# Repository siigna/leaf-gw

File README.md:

# leaf-gw

Decision core for an inline Chassis CAN **gateway** that adds openpilot longitudinal
(gas/brake) control to a 2018–2023 Nissan Leaf (ZE1) **without disabling the
car's stock emergency braking**.

> Bench and a dedicated test car only — never a daily driver. This touches the
> brake path.

## Architecture

The comma/openpilot device, its panda, and this interceptor are **not wired
together** — everything crosses as CAN frames. Thick = the openpilot command;
dotted = the hardware fail-open bypass. Source: [`docs/architecture.mmd`](docs/architecture.mmd).

```mermaid
%% leaf-gw topology. Every link is CAN; arrows show the direction that matters.
%% Thick = the openpilot command; dotted = the hardware fail-open bypass.
flowchart TB
  subgraph COMMA["comma / openpilot"]
    direction TB
    OP["controlsd + CarController<br/>leaf_gw_long.py"]
    PANDA["panda · safety gate"]
    OP --> PANDA
  end

  subgraph INT["leaf-gw interceptor — Ocelot, 3x CAN"]
    direction TB
    CORE["gw_engine<br/>decode · arbitrate · encode · fail-open"]
    RELAY["NC fail-open relay"]
  end

  subgraph CAR["Nissan Leaf ZE1 (stock)"]
    direction TB
    ADAS["ADAS unit<br/>ProPILOT / ICC / AEB"]
    RADAR["radar + camera"]
    EPS["EPS steering"]
    VCM["VCM"]
    ABS["ABS actuator"]
    RADAR --- ADAS
  end

  VCAN{{"V-CAN<br/>(steering + openpilot 0x2B0/0x1C3)"}}
  ITS{{"ITS-CAN"}}
  ICA{{"Chassis CAN · ADAS side"}}
  ICB{{"Chassis CAN · chassis side"}}

  %% V-CAN is shared: panda already sits here. Steering goes to EPS; openpilot's
  %% real 0x2B0/0x1C3 ride the same bus and the interceptor reads them on CAN3 (a tap).
  PANDA -->|steering| VCAN --> EPS
  PANDA ==>|0x2B0 / 0x1C3 · bus 2| VCAN
  VCAN ==>|CAN3 tap| CORE
  ADAS --- VCAN
  %% ADAS private sensor bus
  ADAS --- ITS
  RADAR -.-> ITS
  %% stock request in -> arbitrated -> out to the brakes
  ADAS -->|0x2B0 / 0x1C3| ICA --> CORE
  CORE -->|0x2B0 / 0x1C3| ICB --> ABS
  ICB --> VCM
  %% hardware fail-open
  ICA -. bypass on reset .-> RELAY -.-> ICB

  classDef bus fill:#fff6d5,stroke:#b59a00
  classDef ic fill:#fde8e8,stroke:#cc6666
  classDef relay fill:#fdd6d6,stroke:#cc0000
  class VCAN,ITS bus
  class ICA,ICB ic
  class RELAY relay
```

That graph is the wiring *logically*. For **what happens over time** in one
engaged longitudinal cycle — who sends what, and the arbitration / fail-open
branches — the sequence chart (source: [`docs/sequence.mmd`](docs/sequence.mmd)):

```mermaid
%% leaf-gw: one engaged longitudinal control cycle, plus the safety branches.
%% Rendered inline by GitHub from the fenced copy in README.md.
sequenceDiagram
  autonumber
  participant OP as openpilot<br/>controlsd + CarController
  participant PA as panda<br/>safety
  participant GW as leaf-gw<br/>gw_engine
  participant AD as ADAS unit
  participant AB as ABS / VCM

  Note over OP,AB: Lateral is a separate path: OP → panda → V-CAN → EPS,<br/>it does NOT pass through the gateway. Below is longitudinal only.
  Note over AD,AB: The stock ADAS unit is never<br/>silenced — it keeps emitting its<br/>own 0x2B0 / 0x1C3 the whole time.

  GW-)PA: 0x5FF heartbeat, 50 Hz (V-CAN)<br/>no heartbeat → no long toggle, panda drops control

  loop every ~10 ms
    AD->>GW: 0x2B0 / 0x1C3 stock request<br/>(Chassis CAN ADAS side → CAN1)
    OP->>PA: desired accel (m/s²)
    alt engaged AND within bounds
      PA->>GW: real 0x2B0 / 0x1C3<br/>(V-CAN → gateway CAN3)
    else disengaged / out of bounds
      PA-xGW: blocked — panda sends nothing
    end

    alt openpilot fresh (< 50 ms) AND engaged
      Note over GW,AB: arbitration — forward whichever<br/>side commands MORE braking (op vs stock)
      GW->>AB: substituted 0x2B0 / 0x1C3<br/>(chassis side → ABS)
    else stale / disengaged
      GW->>AB: stock frame forwarded unchanged
    end
  end

  Note over AD,AB: Stock AEB = a hard 0x1C3 spike from the<br/>ADAS unit. Arbitration forwards it (stock ><br/>op), so emergency braking always wins.
  Note over GW,AB: MCU reset / power-loss → external NC relay<br/>reconnects ADAS ↔ chassis directly = stock<br/>path (no software involved).
```

And the **physical wiring** (planned; source: [`docs/wiring.mmd`](docs/wiring.mmd)).
It builds on comma's own Nissan A car harness, which plugs in between the ADAS
unit and the car loom and already brings the two halves of Chassis CAN out on
separate wire pairs; the harness box normally just joins them. The gateway sits
in that join, on a modified car-harness cable. The car's wiring is never cut,
the harness box and comma stay stock, and swapping the original cable back
undoes it. Pins and build steps are in [`HARDWARE.md`](HARDWARE.md):

```mermaid
%% leaf-gw PLANNED wiring, built on comma's Nissan A car harness (no cuts to the car).
%% The car-harness cable plugs in between the ADAS unit and the car loom and brings both
%% halves of Chassis CAN out separately; the gateway sits where the harness box would
%% join them. Pins from comma's open Nissan A drawing + the 2018 ESM. Bench only.
flowchart LR
  ADAS["ADAS unit<br/>stays LIVE (AEB intact)"]
  LOOM["car loom<br/>EPS · VCM · ABS"]

  subgraph CABLE["modified car-harness cable"]
    direction TB
    A["ADAS-side connector"]
    C["car-side connector"]
    A ---|"pass-through<br/>PT1–PT12"| C
  end

  subgraph GW["leaf-gw gateway (our add-on)"]
    direction TB
    CAN1["CAN1 · Chassis ADAS side"]
    CORE["gw_engine"]
    CAN2["CAN2 · Chassis car side"]
    CAN3["CAN3 · V-CAN tap"]
    RELAY["NC fail-open relay"]
    CAN1 --> CORE --> CAN2
    CAN3 --> CORE
  end

  subgraph STOCK["stock comma install (unchanged)"]
    direction TB
    HB["harness box<br/>V-CAN relay (steering)"]
    CF["comma four"]
    HB ---|OBD-C| CF
  end

  ADAS --- A
  C --- LOOM

  A ==>|"Chassis CAN<br/>pins 8/9 → CAN1"| CAN1
  CAN2 ==>|"Chassis CAN<br/>→ car pins 8/9"| C
  A -.->|"NC bypass"| RELAY -.-> C

  A -->|"V-CAN pins 1/2<br/>(box 16/18)"| HB
  A -.->|"tap"| CAN3
  C -->|"V-CAN (box 4/6)"| HB
  CAN2 -->|"box 8/7 → comma bus 1"| HB

  classDef stock fill:#e6f2e6,stroke:#44aa44
  classDef addon fill:#e6e6fb,stroke:#5555cc
  classDef cable fill:#fff6d5,stroke:#b59a00
  classDef relay fill:#fdd6d6,stroke:#cc0000
  class CF,HB stock
  class CAN1,CAN2,CAN3,CORE addon
  class A,C cable
  class RELAY relay
```

## How StarPilot does it, and why we don't silence

StarPilot has the one known Leaf-longitudinal implementation — but it's
**disabled** in the tree (`ALPHA_LONG_ENABLED = False`) and pinned to a single
2025 SV Plus camera firmware. It's one developer's experiment, not a shipped or
widely-run feature (StarPilot's public car list shows the Leaf for *steering*,
and says nothing about longitudinal). It still shows both that these frames
actuate on that car and why nobody kept AEB. On engage it opens a KWP2000 session
to the ADAS ECU (`0x707`) and sends *DisableNormalMessageTransmission* (`28 02`),
held open with tester-present, so the ADAS unit **goes mute**; openpilot then
transmits its own `0x2B0`/`0x1C3` on the chassis-side bus with no competing
transmitter.

That mutes **everything** the ADAS sends — including the emergency braking it
would command. No ADAS, no AEB. We reuse its accel→frame math, but treat the
numbers as a lightly-proven starting point (see the caveat below), and we do
**not** silence anything.

Instead the ADAS stays live (AEB included) and the in-line gateway **arbitrates**
per frame — dropping the ADAS's `0x2B0`/`0x1C3` only when openpilot asks for more
braking, re-stamping the stock counter so the stream stays valid. A plain
comma-harness-plus-panda can't do that (it can only add frames, not replace a
running counter-stream), which is the whole reason this is a separate in-line box
rather than a pure openpilot port.

## Why the frames are inert without the gateway

openpilot emits the real `0x2B0`/`0x1C3` on V-CAN, but on the ZE1 those ADAS
actuation signals live on **Chassis CAN** — a bus the comma harness only *listens*
to, never injects onto. So a `0x2B0`/`0x1C3` sent on a comma-accessible bus
reaches no actuator; only this interceptor, spliced into Chassis CAN, can relay them
to the ABS/VCM. Hence:

- stock car, or interceptor absent / dead → the frames go nowhere (inert);
- the gateway is the *enabling* piece, not an optimization.

Independent support: Nissan's own gateway forwarding table (published in
PCAutomotive's Black Hat Asia 2025 Leaf talk) forwards only diagnostic and a few
status IDs between buses (`0x49F`, `0x620-0x621`, `0x6FA`, `0x700-0x7FF`, …) —
`0x2B0`/`0x1C3` are not forwarded, so the car's gateway won't bridge them to the
actuators either.

That is also why mainline openpilot has no Leaf longitudinal: the only known way
to actuate was to silence the ADAS ECU and transmit on a bus that reaches the
brakes (StarPilot) — which kills AEB. This gateway actuates by splicing Chassis CAN
instead, so stock AEB stays.

**Safety gate:** across 37 cars, stock `0x2B0`/`0x1C3` show up only on panda
bus 1, never on bus 2, so nothing stock competes with openpilot's frames there.
That doesn't prove an injected frame is inert: "inert" is a property of the
*bus*, not the frame, and StarPilot proves these IDs bite on a bus that reaches
the ABS. So confirm the V-CAN segment
we transmit on is listen-only: with the interceptor absent, inject `0x2B0`/`0x1C3`
there and verify **no actuation** and that **nothing crosses to Chassis CAN**. (Same
bench step as pinning which V-CAN segment is panda bus 2.)

## What's here

`leaf_gw.c` / `leaf_gw.h` — pure, hardware-independent logic, host-testable:

- decode/encode of the two ADAS request frames, `0x2B0` (propulsion/regen → VCM)
  and `0x1C3` (friction brake → ABS actuator), plus the `0x1C3` checksum and
  `0x2B0` inverse-copy validation;
- `leaf_mode()` — fail-open state: `ACTIVE` only while engaged and an openpilot
  command arrived within the timeout; otherwise `PASSTHROUGH` (stock);
- magnitude arbitration — the gateway never silences the ADAS unit, so the stock
  request stays live; `leaf_arb_*` forward whichever side commands more braking
  and always yield to a stronger stock request. That is how stock AEB survives.
- the gateway **heartbeat** (`0x5FF`, 50 Hz, sent on the V-CAN port): openpilot
  only offers longitudinal when it sees it at startup, and panda drops control if
  it stops, so openpilot can't think it is driving when no gateway is inline.

```sh
make test
```

## Nix

```sh
nix flake check                 # C core + both Python suites + the Ocelot firmware build
nix build                       # build + host-test the core
nix build .#ocelot-firmware     # the signed panda/Ocelot image (leaf_gw.bin.signed, .elf, .bin)
echo '(0) can0 1C3#000000006400FF27' | nix run .   # phase-0 validator on a candump log
nix develop                     # host dev shell (gcc, make, python+numpy)
nix develop .#panda             # arm-none-eabi + scons, to build the Ocelot backend by hand
nix develop .#openpilot         # python 3.12 + opendbc test deps, to run the car/safety patches
nix develop .#hardware          # the board (hardware/board): KiCad, SKiDL, freerouting
nix develop .#enclosure         # the case (hardware/enclosure): .#hardware plus OrcaSlicer, gmsh
```

`nix build .#ocelot-firmware` is a sealed, offline build: it pulls the RetroPilot
ocelot tree (a pinned flake input), drops this repo's `backends/panda/` + the core
into it, registers the scons project and signs with the debug cert.

## openpilot side

`openpilot/` has the car-side piece: an opendbc `car/nissan` patch that, with longitudinal enabled, emits the car's **real** `0x2B0`/`0x1C3` frames on V-CAN (panda bus 2) — no ECU silencing, no cruise spoofing, so stock AEB stays. The inline gateway reads them off V-CAN and re-emits onto Chassis CAN with magnitude arbitration. panda bounds the frames with the standard longitudinal safety helpers. `leaf_gw_long.py` is the dependency-free mapping/packer spec (host-tested, `python3 openpilot/test_leaf_gw_long.py`); the patches wire it into opendbc. See `openpilot/README.md`.

## What's NOT here (by design)

- The firmware CAN forwarding loop (that's `backends/panda/`, built against an
  Ocelot tree — see `nix build .#ocelot-firmware`).
- The **hardware normally-closed fail-open relay** that reconnects ADAS-side
  Chassis CAN straight to the chassis side when the MCU is unpowered/reset. Software
  cannot provide power-loss fail-open; the relay is mandatory.

Those are integration + hardware and are not unit-testable on a host.

## Big caveat

The `0x2B0`/`0x1C3` layouts started from StarPilot's **disabled, firmware-pinned
2025-SV-Plus experiment**. Stock logs from 38 ZE1s have since replaced most of
it: the `0x2B0` value field, its direction and a provisional accel scale now come
from stock data. Brake pressure scaling is still StarPilot's and unverified, and
nothing has been transmitted to a car.

- **The `0x2B0` value is T = `(b2 << 4) | (b1 & 0xF)`**, a 12-bit field whose
  inverted copy sits in `b1_hi:b0`. **Higher T = more deceleration.** StarPilot's
  packer scrambled it, so its accel map was meaningless for most of its range
  (its "0 m/s²" lands at T 2304, about +0.6 m/s²). Found in two steps: the public
  US route showed the low nibbles out of order, then SHIOKAZE showed the top nibble
  was inverted too. On ~755k frames from 38 cars the inverted copy holds on every
  frame and T moves smoothly (mean step 0.18 counts; big jumps are engage/idle
  transitions).
- **Stock values:** idle / inactive T = 2595 (`dc 53 a2 .. 1b .. 03`), the
  friction-brake marker T = 3415 (`a8 27 d5 .. 5b .. 09`, only while `0x1C3`
  pressure > 0: 822 of 835 frames on the US route, 8,718 of 8,718 on SHIOKAZE's
  car), and active values in 2048..3071. "More braking" is simply the larger T,
  marker included, which is what the gateway's arbitration uses.
- **Byte 3 is a state field.** Its low nibble is always `0xC`; the top three bits
  vary (`ac`, `8c` in Park, `6c`, `4c`, …) across all cars. The gateway keeps
  stock's byte 3 when it substitutes. Bit `0x20` tracks "cruise available"
  (openpilot's `CRUISE_THROTTLE.CRUISE_AVAILABLE`): SHIOKAZE found it on their
  car, and it agrees on 99.95% of the fleet sample's 755k frames, the rest at
  on/off transitions. Byte 4 bit `0x40` is "engaged and moving".
- **`0x180` follows T about 160 ms later** (SHIOKAZE): a signed 12-bit value in
  byte 2 and byte 3's top nibble, D ≈ −0.796·T + 2067. On the fleet sample it is
  on panda **bus 0** for Nissan A cars, and the best segments fit D = −0.798·T +
  2070 at correlation −0.999 (RMSE 1.1); the median segment's RMSE is 8, and it
  departs when something else (pedal, friction brake) drives the car. Whether it's
  the VCM's actual response or just a reflection of the request is open, but
  since the comma can read it directly, the openpilot patches use it as a
  follow check: if the car slows less than openpilot asked for 1 s, openpilot
  disengages (see `openpilot/README.md`).
- **Accel scale (provisional):** fitting acceleration measured from wheel speed to
  T during ICC, across the 37-car sample, gives correlation −0.76. Zero is near
  T ≈ 2530, about +0.8 m/s² at 2272 and −0.8 at 2784, flatter in between. The
  openpilot mapping interpolates those medians. It needs an active bench or
  test-car check before anyone relies on it.
- **Public route** `44211d9f2879657d/00000024--ddf4161f21` (US `NISSAN_LEAF_IC`,
  sunnypilot, stock ICC engaged 61% of the time; 23,959 frames of each id on
  bus 1): every `0x1C3` checksum and every `0x2B0` inverse copy validates.
- **SHIOKAZE** (openpilot Discord, 2026-11-24; receive-only logs from a June 2022
  Japanese-spec ZE1 e+ G, bus 1 via the Nissan IC harness): independently
  confirmed the `0x1C3` field and checksum, worked out the `0x2B0` value field
  (T), the brake-marker state and that `b4 & 0x40` means engaged and moving, and
  found `0x707` `28 02` refused (`7F 28 11`), so StarPilot's silencing route
  doesn't work on that car.
- **Fleet check** (comma's public [commaCarSegments](https://huggingface.co/datasets/commaai/commaCarSegments)
  dataset; 3 segments from each of 31 Nissan A-harness and 6 IC-harness Leafs,
  106 segments, 635k frames of each id): zero checksum / inverse-copy failures,
  and the brake marker bytes are identical everywhere. Stock `0x2B0`/`0x1C3` appear **only on bus 1**,
  on both harnesses, never on bus 0 or 2, so stock never competes with
  openpilot's frames on bus 2. `0x5FF` never appears on any bus, so the
  heartbeat id is free.
- **What stock braking looks like.** The highest `0x1C3` pressures (680–821) are
  all ICC's standstill hold: the car stops, `0x2B0` goes to the brake marker,
  `0x1C3` ramps at ~280 counts/s, and ICC releases a few seconds later. The
  strongest braking while moving was a sudden ICC brake at 68 km/h (0 → 556 in
  under a second, about −2 m/s²) that ended when the driver pressed the
  accelerator. Arbitration handles both (stock is stronger, so stock wins); no
  AEB event is in the sample.
- Still open: the brake pressure scaling, whether `0x1C3` is total or
  friction-only braking, and what byte 3's state bits and byte 7's 2-bit field
  mean.

Check your own car with the read-only validator `tools/leaf_iccan_check.py`:
capture Chassis CAN (panda + Cabana, USB-CAN, or `candump`) and feed it the log.
It checks the `0x1C3` checksum, the `0x2B0` inverse copy, and that the `0x2B0`
value moves smoothly (a wrong bit order can pass the inverse copy but not that).

Our test car (2018 SL, 40 kWh), ECU part/version from Leaf Spy: FRONT CAMERA
`28438`/`5SA0A`, RADAR `28438`/`5SA0C`, ABS `47660`/`5SA0A`, BRAKE `47880`/`5SA1B`,
MOTOR CONTROL `292C0`/`5SA1A`. Leaf Spy's short version codes are probably a
different identifier from StarPilot's `6WK2CDB` camera pin, so the mismatch proves
nothing.

## License

MIT (see `LICENSE`), so the openpilot community can reuse it freely and because
the CAN message formats derive from MIT opendbc/StarPilot. Credits in
`ATTRIBUTION.md`.

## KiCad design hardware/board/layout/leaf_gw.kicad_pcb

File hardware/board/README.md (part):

# leaf-gw board

The inline gateway board from [SPEC.md](SPEC.md). Phase 2 is the schematic as
SKiDL code, the BOM with LCSC numbers, and the checks that stand in for a
schematic review. Phase 3 is the layout: a 75 × 50 mm, 4-layer board built by
script from the netlist, routed (pairs by script, the rest by freerouting),
checked, and turned into JLCPCB fab files. Nobody reviews the layout by eye, so
the checks are the review; each of them has a mutation test that proves it
fails on a broken board.

## Files

| path | what |
|---|---|
| `SPEC.md` | the contract |
| `ORDER.md` | how to order from JLCPCB (files, options, what to check in the preview) and how to make the board-to-box cable |
| `schematic/` | SKiDL, one module per block: `connectors`, `mcu`, `can`, `relay`, `power`, `usb`; `parts.py` holds every part with its LCSC number; `nets.py` names the nets; `board.py` builds the board and writes `out/` |
| `footprints/leaf_gw.pretty/` | project footprints for parts KiCad's library lacks (the Molex iGrid header) |
| `out/leaf_gw.net` | KiCad netlist, for phase 3 to import into the PCB |
| `out/bom_jlcpcb.csv` | JLCPCB BOM: Comment, Designator, Footprint, LCSC |
| `out/parts.csv` | the same parts with manufacturer, MPN, JLC basic/extended and stock as checked |
| `out/no_connects.csv` | every pin left unconnected on purpose, with its reason |
| `checks/` | netlist reader, safety-net checks, BOM/footprint checks, mutation tests; `layout.py` and `test_layout_mutations.py` for the PCB |
| `check.sh` | runs the schematic checks (`board-schematic`) |
| `layout/` | the PCB build: `build.py`, `placement.py`, `routes.py`, `repair.py`, `board.py` (rules, stack-up, net classes), `impedance.py`, `logo.py`, `fab.py`, `render.sh` |
| `layout/leaf_gw.kicad_pcb`, `.kicad_pro`, `.kicad_dru` | the generated board, project (net classes, JLC rules) and custom DRC rules |
| `out/fab/` | gerbers + drill, `leaf_gw-gerbers.zip`, JLC BOM and CPL, the CPL rotation corrections with their sources |
| `out/render/` | `top.png`, `bottom.png` (3D) and SVG plots of each copper layer and the assembly view |
| `check_layout.sh` | runs the PCB checks (`board-layout`) |

`out/` and `layout/leaf_gw.*` are generated, but committed so the next phase
and the board house have them; the checks fail if they are stale.

There is no `.kicad_sch`: SKiDL 2.2.1 generates schematics only for KiCad 5 to
8 (`gen_schematic` for KiCad 9 and later is an unimplemented stub), and KiCad 10's
libraries are what nixpkgs ships. The netlist is the design's source of truth
between phases.

## Running the checks

```bash
nix develop .#hardware --command ./hardware/board/check.sh            # check
nix develop .#hardware --command ./hardware/board/check.sh --update   # after editing schematic/
nix flake check                                                       # includes board-schematic and board-layout
```

`nix flake check` copies the flake's git tree, so new files have to be
`git add`ed before it sees them.

Stages, in order (one failing stage doesn't stop the others):

1. **Build + SKiDL ERC.** Any ERC error or warning fails. Unused pins are
   connected to `NC` only through `nets.nc(pin, reason)`, which records the
   reason in `out/no_connects.csv`; every other unconnected pin is an ERC warning.
2. **Freshness.** `out/` must match a fresh build byte for byte.
3. **Safety-net checks** (`checks/safety.py`), on the netlist file and
   independent of the SKiDL code (expected pin numbers come from the
   datasheets, roles from SPEC.md's tables):
   - pass-through: pins 3, 5, 13, 15, 4, 6, 10, 12 join J1.n to J2.n and nothing
     else; GND, IGN, V-CAN ADAS-side and car-side CAN1 join J1 and J2 with no
     other harness pin; IGN enters the board only through the fuse;
   - box-side J2.9 / J2.11 connect to nothing;
   - relay: pole A COM on J1.9, NC on J1.8; pole B COM on J1.11, NC on J1.7;
     NO contacts open; the two CAN1 halves are not hard-wired;
   - CAN lines: each line holds exactly its harness pins, one transceiver pin
     (CANH on H), one ESD pin, one termination jumper and, on CAN1, its relay
     contact. Termination is default-open jumper → 60.4 Ω → split midpoint
     → 60.4 Ω → jumper, midpoint → 4.7 nF → GND. Anything else on a CAN line
     fails, so a CAN line has no other path to power or ground;
   - coil driver: coil+ on the IGN-derived 5 V, coil− on the low-side FET drain
     with a flyback diode; the gate net holds only the AND output and one
     pull-down; AND input A is PB12 with one pull-down; input B is the
     open-drain watchdog RESET, which is also MCU NRST; WDI is driven only by the
     kick pin;
   - USB isolation: the coil supply is not DC-reachable from VBUS (diodes
     forward only), and it is reachable from IGN;
   - MCU pins, by LQFP64 pin number: CAN1/2/3 RX/TX and standby go to the
     transceiver on the right bus, PA1 to the IGN divider, PA11/PA12 to USB D−/D+;
     no two table pins share a net.
4. **BOM + footprints** (`checks/bom.py`): every assembled part has an LCSC
   number and a JLC library type; designators are unique in the netlist and in
   the CSV; the CSV lists exactly the assembled parts; parts off the BOM are bare
   copper (test pads, solder jumpers) with a reason. Every footprint exists and
   has a pad for each connected pin.
5. **Mutation tests** (`checks/test_mutations.py`): 41 in-memory mutations of
   the real netlist, each of which must make its check fail (relay NC/NO
   swapped, poles crossed, box 9/11 connected, gate pull-down dropped, gate fed
   from PB12 directly, watchdog off NRST, CAN1 on the CAN2 pins, RX/TX swapped,
   resistor from a CAN line to GND, closed termination jumper, coil on the USB
   rail, OR diode reversed, missing LCSC, duplicated designator, pin without a
   pad, and more), plus the unmutated netlist passing everything.

## Layout (phase 3)

### Pipeline

`layout/build.py` builds `layout/leaf_gw.kicad_pcb` from `out/leaf_gw.net`.
It takes about 40 minutes, most of it in the pre-route searches and freerouting.

1. **Project and rules.** It writes `leaf_gw.kicad_pro` (net classes, the JLC
   minimums, DRC severities) and `leaf_gw.kicad_dru` (12 V track width, via
   drill and ring).
2. **Board.** A 75 × 50 mm outline with 1 mm corner radii goes on a 4-layer
   board. Every footprint comes from the netlist with its fields and pad nets,
   placed by `placement.py`, all on the top side. Two M2 mounting holes go in
   opposite corners.
3. **Critical routes by script** (`routes.py`). The four CAN pairs and the USB
   pair are drawn coupled at the impedance geometry, split evenly around their
   tap clusters, and length-matched with small rectangular bumps (`TUNE`).
   freerouting has no differential-pair support, so the pairs never reach it.
   The same file draws a few hand routes into spots freerouting can't reach:
   CC1, SWDIO, the MCU supply pins boxed in by their neighbours, and the
   USBLC6's VBUS via. It also draws the short local copper that must not be
   left to chance (`LOCAL_LINKS`, `POWER_LINKS`): each transceiver's VCC and
   VIO cap, U5/U6's supply cap, the termination chains off the relays' NO
   contacts, the two coils in parallel, and the buck's own copper (switch
   node, hot-loop VIN and GND, bootstrap, feedback and its sense at the output
   cap, the input protection).
4. **Fanout** (`build.fanout`). Each SMD pad on GND or +3V3 gets a via to its
   plane. So does each signal pin the CAN lines close in on (`routes.FANOUT_SIGNALS`).
   A spot is accepted only where the via's In1 antipad stays clear of the GND
   plane under the pairs, and where its ring keeps `board.VIA_PAD_WEB` from
   every SMD pad, its own net's included (no via in or touching a pad).
5. **Pre-routes** (`repair.preroute`, list in `routes.PREROUTE`). The
   transceivers' STB lines and the MCU's top-row CAN pins and BOOT0 are
   routed first with the
   grid router (step 8), while the board is still open. Each search is capped
   (8 M expansions, 900 s, a box 14 mm around its ends) and logs why it gave
   up; whatever fails is left to freerouting.
6. **Silkscreen.** Library silkscreen that would print on a pad or overlap
   other silkscreen is dropped (`silk_cleanup`). Then the logo, the text, the
   back-side pin names and the bench warning go on, and a cathode bar beyond
   pad 1 of every diode and LED whose library mark was dropped
   (`polarity_marks`).
7. **freerouting.** The board is exported to DSN and the DSN is patched. In1
   and In2 become power layers, so nothing routes on them. The pairs and the
   plane nets leave the network, and their copper turns into keepouts. Each
   pair also gets a via keepout as wide as the reference-plane check needs,
   and the strip between J2's edge-side pin row and the board edge gets one
   too (`routes.VIA_KEEPOUT`: via antipads there pinch the In2 plane). New vias
   use a padstack 0.05 mm wider than the real one, so freerouting's via-to-via
   clearance also keeps 0.5 mm hole to hole; they are shrunk back after the
   import. The DSN also says `via_at_smd off`, and B.Cu under the buck's
   switch node and L1 is a keepout (`build.quiet_zone`). freerouting 2.5 then runs single-threaded (`-mt 1`) with a fixed
   pass count (wall time capped at 900 s), and the SES is imported back.
8. **Repair.** If freerouting leaves anything open, `repair.py` routes it on a
   0.05 mm grid (A* over F.Cu and B.Cu with vias, capped at 4 M expansions
   and 240 s per search), clear of every other net's copper, of the via
   keepouts and, for its vias, of every SMD pad. On the committed board freerouting finished everything, so the
   repair had nothing to do.
9. **Clean-up and zones.** Tracks that freerouting necked below the minimum
   are widened back where there is room (`widen_necks`); one that can't be
   widened is taken out and its gap repaired at full width. Every lone via
   on a 12 V or 5 V net gets a twin 0.85–1.4 mm away, joined on both layers
   (`twin_power_vias`). The zones go on: In1 solid GND, In2 solid +3V3, and
   GND pours on F.Cu and B.Cu with thermal reliefs, and are filled. Then
   `stitch_gnd` puts GND vias along the board edge about every 5 mm where
   both pours leave room, gives every outer pour island at least two vias to
   In1, and cuts an island that can't take them out of its pour (a rule
   area), unless a pad hangs on it alone. Then `drop_dangling` deletes every via joined on
   fewer than two layers and every track with a loose end (freerouting's
   leftovers, fanout and escape vias it bypassed), one at a time and only if
   nothing comes apart without it.
10. **Normalise.** Every UUID is renumbered in file order from a fixed
   namespace, so the same inputs give the same file, and `leaf_gw.kicad_pro`
   is written again after pcbnew's save (which rewrites it).

`layout/fab.py` then writes `out/fab/` and `layout/render.sh` writes
`out/render/`.

### Placement

`placement.py` and `routes.py` are drawn on the first, 59 × 39.5 mm board.
That was too dense: freerouting and the repair left 1 to 3 connections open
on every run. `board.spread()` opens the drawing up into the 75 × 50 mm
outline by moving whole blocks rigidly. It adds 1, 10 and 5 mm in x at three
vertical cuts (J1's pin field | the clusters and MCU, ADAS side and relay |
car side, car side | J2's pin field), 3 mm in y below the top band and 7.5 mm
below CAN0, between the headers. Groups that sit in room the spread opened,
or would straddle a cut, are placed and routed in board mm after the spread
(`placement.CAR`, `ADAS_TERM`, `POWER`; `routes.car_side`, `POWER_LINKS`):
the car side right of K1 with K2, both termination chains, the power entry
and the buck, the LDO strip, and U5/U6's supply caps. Nothing in them moves
with a cut. Only straight runs along the shift cross a
cut, so every scripted route keeps its shape (`routes._spread` asserts it),
and the pair lengths change equally on both lines. A 70 × 45 mm version of
the same spread still left one connection open (CAN2_STB, then RELAY_GATE),
so the board went to the 75 × 50 mm limit.

The two headers sit on the short edges in the same orientation: rotation 90,
pin 1 at the bottom, the even row toward +x. Pin n of J1 and pin n of J2 are
then at the same height, so the pass-through nets run straight across. The
blocks are:

| where | what |
|---|---|
| top left | CAN2 (V-CAN tap): ESD array, transceiver 3, termination, between the CAN2 lines; under it the LDO with its caps |
| top right | the buck as one group (below); right of it the power entry: reverse diode, TVS, PTC tapping the B.Cu IGN lane; the power LED; test pads TP7–TP10 |
| middle left | CAN1 ADAS side next to J1: ESD array, transceiver 1 |
| middle | K1 on all four CAN1 lines, between the two halves; the ADAS-side termination along its top, off its NO contacts |
| middle right | K2 on the car-side lines, the car-side termination beside its NO contacts, then the car-side ESD array and transceiver 2 |
| across | CAN0, straight through |
| bottom | MCU (crystal and decoupling at its pins), USB-C on the bottom edge with the USBLC6 beside it, relay driver and watchdog, SWD pads, DFU button, ignition sense |

Each CAN tap cluster sits between its own two bus lines, L over the top and H
underneath. The ESD array (rotation 180, pads 1/2 on its right) faces the
transceiver's CANL/CANH pins (rotation 180, pins 6/7 on its left) across a
0.77 mm channel. Short spurs drop into that channel from each line. This is
how the lines tap the cluster without crossing each other, so the CAN copper
needs no vias at all.

The buck (U7) is one tight group: D8 right above the SW pin, the input caps
right of VIN with C26 first and their GND pads under D8's anode (hot loop
C26–VIN–SW–D8–GND 10.3 mm², from 60.9), L1 beside D8 on the same SW copper
as the bootstrap cap, the output caps under L1's output, and the feedback
divider between them and the FB pin, so FB, CB and the sense at C28 are a few
mm on F.Cu. The output caps' GND is on the far side of the group from D8's
anode (about 12 mm, through the pour and In1 0.2 mm below); keeping both
loops on the same side would have pushed the sense trace and the input feed
across each other.

K2 (rotation 90) takes the car pair through the channel between its pad
rows: the L line leaves up through COM_B and the H line down through COM_A,
so the contacts sit on the lines with no stub, and its NO pads face the
car-side jumpers. Its coil pads sit next to K1's; the two coils are joined on
F.Cu (+5V_IGN) and share the driver and flyback diode.

The relay is DPDT, pole B (L) in the left column and pole A (H) in the right.
ADAS L lands on COM_B from the left. ADAS H passes between COM_B and NC_B to
COM_A from inside. Car L lands on NC_B and leaves between COM_A and NC_A. Car
H passes under NC_B to NC_A. None of the four lines crosses another.

### Stack-up and impedance

JLC04161H-7628, 1.6 mm, as listed at
[jlcpcb.com/impedance](https://jlcpcb.com/impedance) (read 2026-11-26):

| layer | role | copper | to next layer |
|---|---|---|---|
| L1 F.Cu | signal (pairs) | 35 µm | 7628 prepreg 0.2104 mm, εr 4.4 |
| L2 In1.Cu | GND plane | 15.2 µm | core 1.065 mm, εr 4.6 |
| L3 In2.Cu | +3V3 plane | 15.2 µm | 7628 prepreg 0.2104 mm, εr 4.4 |
| L4 B.Cu | signal | 35 µm | |

`layout/impedance.py` computes the pairs as edge-coupled microstrip on L1 over
L2. The single line uses Hammerstad & Jensen with the finite-thickness
correction; the coupling uses Garg & Bahl's even/odd capacitances. Both are
static and ignore solder mask, which lowers the impedance by a few percent.
IPC-2141A is shown as a coarse cross-check:

| pair | width | gap | Zdiff (Garg-Bahl) | IPC-2141A | target |
|---|---|---|---|---|---|
| CAN (4 pairs) | 0.19 mm | 0.20 mm | 120.0 Ω | 111 Ω | 120 Ω |
| USB D+/D− | 0.35 mm | 0.20 mm | 89.8 Ω | 81 Ω | 90 Ω |

As a sanity check, the same single-line model puts 50 Ω at 0.36 mm on this
stack-up. Before ordering, confirm both pairs in JLC's own impedance
calculator, which includes the mask. You may also order "impedance control"
on this stack-up (see Ordering).

### JLCPCB rules

The rules come from [jlcpcb.com/capabilities/pcb-capabilities](https://jlcpcb.com/capabilities/pcb-capabilities)
(multilayer, 1 oz, read 2026-11-26). They live in `layout/board.py` and are
written into the project file:

| rule | board | JLC |
|---|---|---|
| track / space | 0.127 / 0.127 mm (SPEC); net classes 0.15 clearance | 0.09 / 0.09 mm |
| via | 0.3 mm drill / 0.6 mm pad (0.15 mm ring) | 0.15 / 0.25 mm min; ring ≥ 0.15 mm absolute minimum |
| hole to hole | 0.5 mm | 0.2 (vias), 0.45 (pads) |
| copper to routed edge | 0.25 mm | 0.2 mm |
| silkscreen | 0.15 mm line, 1.0 mm text, 0.15 mm from pads | the same |
| 12 V input (IGN, IGN_FUSED, VIN_PROT, VIN12_10/12) | ≥ 0.5 mm (custom DRC rule) | |

Net classes: CAN 0.19 mm, USB 0.35 mm, 12V 0.67 mm, Power 0.4 mm and Default
0.17 mm. Two of these are wider than the floor on purpose. Where freerouting
squeezes between pads it necks a track to about 3/4 of its class width, and
these class widths keep a necked track at or above 0.127 mm and 0.5 mm.

### Checks

`check_layout.sh` (flake check `board-layout`) runs these stages:

1. **Self-checks.** The impedance geometries are within 3 % of target, and
   the logo conversion works: the cleaned leaf has no line or gap under
   0.15 mm, a keyholed polygon with holes survives the round trip, and the
   SVG path parser gets an arc's area right and still reads the old snail.
2. **Freshness.** `leaf_gw.kicad_pro` and `.kicad_dru` match the generator.
3. **DRC.** `kicad-cli pcb drc --severity-all` reports 0 errors, 0 warnings
   and 0 unconnected items, against the JLC rules above. Schematic parity is
   left to stage 4, because there is no schematic.
4. **Layout checks** (`checks/layout.py`). They work on pcbnew's own copper
   shapes, independent of the build scripts:
   - parity: every netlist part is on the board with its footprint, every pad
     has the netlist net of (ref, pad), and pads the netlist leaves open have
     none. Nothing extra is allowed except H1, H2 and LOGO;
   - every footprint is on the top side;
   - pairs: all pair copper is on F.Cu, with no via, at the impedance width.
     The only narrower pieces allowed are the USB plug-flip links within
     2.5 mm of J3. Outside the listed `routes.UNCOUPLED` zones (header pin
     fields, the cluster splits, the relay, the USBLC6, the tuning bumps),
     each line sits exactly width + gap from its partner (±10 µm);
   - mismatch: the H/L copper length from the reference end to each bus end
     and transceiver is under 1 mm. The lengths are computed over the track
     graph and printed;
   - reference plane: under every pair track, the In1 GND fill covers the
     track width plus one prepreg height (0.21 mm) on each side, so there is
     no split, no void and no other net's antipad. The header pin fields and
     the USBLC6 are exempt; their own PTH and via antipads are unavoidable;
   - 12 V: every IGN, IGN_FUSED, VIN_PROT and VIN12 track is ≥ 0.5 mm;
   - keepouts: no other courtyard sits within 0.5 mm of either header body
     (the mating face). The USB-C front is at the bottom edge (−0.1 to
     +0.6 mm), and no courtyard sits in the 12.35 mm plug-overmold zone along
     that edge;
   - copper safety: islands are built by physical overlap of every pad,
     track, via and zone fill, per layer and through the holes, ignoring
     their net labels. No island may join two netlist nets, or a net and an
     open pad, and every net must be one island. The relay COM pads reach
     only the ADAS-side lines and the NC pads only the car side, so the two
     CAN1 halves touch only through the contacts. Box pins J2.9 and J2.11
     touch no track or zone on any layer;
   - silkscreen: the logo, as drawn on the board, has lines and gaps of at
     least 0.15 mm, is about 12 mm wide and sits on the top. No silkscreen on
     either side comes within 0.15 mm of a solder-mask opening or runs off
     the board;
   - pin labels: each header has exactly one back-side label per pin row
     ("n … / n+1 …"), its centre within 0.3 mm of that row's pins, on the
     header's inner side with its near end 0.15 to 5 mm from the pads;
   - In2: only short hops on the +3V3 plane, which stays one region with no
     neck under 1.0 mm (see "Known limits");
   - vias and pads: no via ring overlaps or touches any SMD pad, its own net's
     included, so the hole edge keeps at least 0.15 mm of copper web;
   - polarity marks: every diode and LED has top silkscreen within 1 mm beyond
     pad 1 (the cathode), across at least half the pad's width;
   - power vias: every via on a 12 V or 5 V net has a second via of its net
     within 1.5 mm (the USBLC6's VBUS reference pin, boxed in by the USB pair
     and carrying no load current, is exempt), and the switch node has none;
   - GND stitching: every F.Cu or B.Cu GND pour island reaches In1 through at
     least two vias or plated GND pins, and along the board edge (1 mm in),
     wherever both pours leave room for a via, one sits within 3.5 mm
     (except the via keepout strip beside J2);
   - 12 V off the MCU: no VIN_PROT or IGN_FUSED copper within 3 mm of U1's
     courtyard;
   - switch node: nothing but GND on B.Cu under the buck's switch node and
     L1 (0.3 mm around), and no other net on F.Cu inside L1's courtyard.
5. **Mutation tests** (`checks/test_layout_mutations.py`). Each test loads the
   real board, breaks it in memory and asserts that its check fails for the
   intended reason:

   | mutation | caught by |
   |---|---|
   | two pads' nets swapped | parity |
   | a footprint deleted | parity |
   | an extra footprint added | parity |
   | a capacitor flipped to the bottom | top side |
   | a CAN0_L run moved 0.3 mm | pairs (uncoupled) |
   | a via dropped into CAN0_H | pairs (via) |
   | a CAN2_L run moved to B.Cu | pairs (layer) |
   | a USB D+ run narrowed to 0.2 mm | pairs (width) |
   | a 1.2 mm detour added to CAN0_H | mismatch |
   | a 1 mm slot cut in In1 under CAN0 | reference plane |
   | the In1 GND zone deleted | reference plane |
   | an IGN track narrowed to 0.3 mm | 12 V width |
   | a resistor moved onto J1's mating face | keepouts |
   | J3 moved 2 mm in from the edge | keepouts |
   | a resistor moved into the USB plug zone | keepouts |
   | a track across relay COM_A to NC_A | copper safety (short) |
   | the ADAS L track to COM_B removed | copper safety (open) |
   | a track touching J2.9 | copper safety (box pin) |
   | a pass-through loop's tracks removed | copper safety (open) |
   | the logo moved onto MCU pins | silkscreen (pad opening) |
   | a 0.1 mm line added to the logo | silkscreen (line width) |
   | a J2 pin label moved 1 mm off its row | pin labels |
   | a relay K2 COM track removed | copper safety (K2) |
   | a GND fanout via moved onto C26's pad / its ring 0.2 mm into the pad | vias and pads |
   | D6's cathode mark removed | polarity marks |
   | a +5V_IGN via's twin removed | power vias |
   | a via on the switch node | power vias |
   | one of the two vias of a GND pour island removed | GND stitching (island) |
   | the GND vias along the middle of the top edge removed | GND stitching (edge) |
   | a VIN_PROT track across the MCU | 12 V off the MCU |
   | an IGN_SENSE track on B.Cu under L1 | switch node |
   | a 10 mm SWDIO track on In2, In2 split, In2 neck | In2 |
   | a CAN0_H stub run into CAN0_L, saved and run through `kicad-cli pcb drc` | DRC |

   The unmutated board must pass every check.
6. **Fab outputs.** `fab.py` must reproduce `out/fab/` byte for byte. The fab
   BOM must match `out/bom_jlcpcb.csv` part for part (LCSC, footprint, MPN),
   every BOM line must have an LCSC number, and the CPL must list exactly the
   BOM parts.

`./check_layout.sh --rebuild` also builds a fresh board in /tmp/lgw/rebuilt
and requires it to pass the DRC and the layout checks. That takes about 40
minutes, so the flake check leaves it out. Fresh builds don't reliably
converge yet (see "Known limits").

Silkscreen-only changes don't need a re-route: `kicad-python build.py
--silk-only` (in `layout/`) redraws the logo and all silkscreen text on the
saved board from `placement.py` and `logo.py` and leaves copper and fills
alone.

### Regenerating

```bash
nix develop .#hardware --command ./hardware/board/check_layout.sh --update   # rebuild board, fab, renders; then check
nix develop .#hardware --command ./hardware/board/check_layout.sh            # check only
```

After editing `placement.py` or `routes.py`, look at the mismatch report that
`checks/layout.py` prints and adjust `routes.TUNE` if a pair moved.

### Ordering (JLCPCB)

**PCB:** upload `out/fab/leaf_gw-gerbers.zip`. Pick these options:

- Layers 4, dimensions 75 × 50 mm (detected), thickness 1.6 mm, FR-4.
- Impedance control yes, stack-up JLC04161H-7628. That is the stack-up the
  pair widths were computed for.
- Via covering tented, which is what the board assumes; silkscreen runs over
  vias.
- Green mask, white silkscreen. Surface finish: HASL lead-free, or ENIG for
  the 0.5 mm-pitch MCU.
- Remove order number: "specify a location" or pay to remove it. There is no
  marked spot, so pick "remove".
- Board outline tolerance standard. Leave edge rails and tooling holes to
  JLC's assembly options.

**Assembly:** PCBA on the top side, Standard (not Economic). The board has
through-hole headers and extended parts. Upload:

- `out/fab/leaf_gw-bom.csv` as the BOM. All 37 lines have LCSC numbers.
- `out/fab/leaf_gw-cpl.csv` as the CPL. Mid X/Y are in mm from the board's
  bottom-left corner, all parts on the top.

In the placement preview, check every part listed as "verify" in
`out/fab/leaf_gw-cpl-corrections.csv`. Those are the relay, the MCU, the
SOT-23-6 parts, the iGrid headers and every polarized two-terminal part,
whose rotations come from footprint-family tables rather than part-specific
evidence. Adjust the rotations there if a body or pin-1 mark is off. The
headers J1/J2 are through-hole on the top side; JLC solders those by
selective/wave or by hand as part of Standard PCBA. Buy the MCU (C468260,
90 in stock on 2026-11-26) early.

**The box cable** is a separate order. It is a 501646-1800 receptacle on both
ends, crimped 501647-1000 terminals, pin n to pin n, positions 9 and 11 left
empty, 26 AWG, about 100 mm. Order it from a harness service with a drawing,
for example LCSC Cable ([lcsccable.com](https://lcsccable.com), no MOQ). See
"Connectors" above for the part numbers. Leaving positions 9 and 11 empty is
part of the safety design, so state it on the drawing.

### Known limits of the layout

- **Routing is complete.** The committed board is a fresh `build.py` output
  (no hand edits): DRC 0 errors, 0 warnings, 0 unconnected, and every layout
  check and mutation test passes. The pre-order review revision was validated by two fresh
  `check_layout.sh --rebuild` runs on 2026-11-27, both valid on the first
  routing attempt; an earlier pair had one run leave SWCLK unrouted on all six
  attempts, so SWCLK is now pre-routed (`routes.PREROUTE`).
- **The buck's output loop closes through the pour.** The output caps' GND
  sits about 12 mm from D8's anode, on the far side of the group (see
  "Placement"); the return runs in the F.Cu pour and the In1 plane 0.2 mm
  below. The input hot loop, the one with the fast edges, is 10.3 mm².
- **USBLC6 VBUS has one via.** U9's VBUS pin is the clamp's reference and
  carries no load current; it is boxed in by the USB pair, so its single via
  is exempt from the twin-via rule. The load path from J3 to D10 has twins.

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
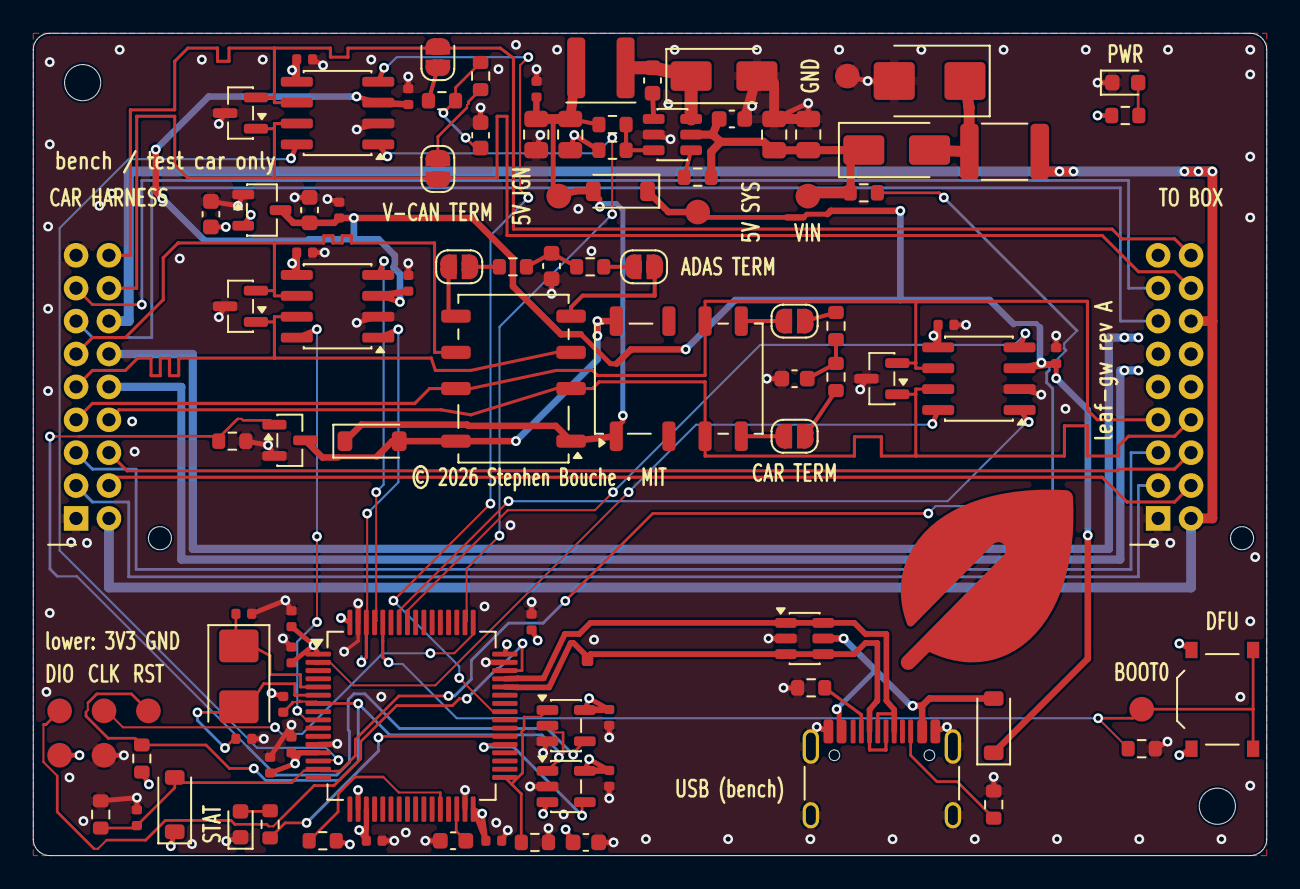
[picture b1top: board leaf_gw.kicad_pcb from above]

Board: 4 copper layers, 75.0 x 50.0 mm, 104 parts (0 on the bottom side), 68 nets.

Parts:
C1, C8, C31, C33: 4.7uF 16V; C_0603_1608Metric
C2, C3, C4, C5, C6, C7, C13, C14, C16, C17, C19, C20, C22, C23, C30, C34: 100nF 16V; C_0402_1005Metric
C9, C32: 1uF 25V; C_0402_1005Metric
C10, C11: 30pF C0G; C_0402_1005Metric
C12: 10nF 50V; C_0402_1005Metric
C15, C18, C21: 4.7nF 50V; C_0603_1608Metric
C24, C25: 2.2uF 50V X7R; C_0805_2012Metric
C26, C27: 100nF 50V; C_0603_1608Metric
C28, C29: 22uF 25V; C_0805_2012Metric
D1: STATUS; LED_0603_1608Metric
D5, D12: 1N4148W; D_SOD-123
D6: SMBJ33A; D_SMB
D7, D8: SS210; D_SMA
D9, D10: B5819W; D_SOD-123
D11: PWR; LED_0603_1608Metric
D21, D22, D23: PESD2CAN; SOT-23
F1: 500mA hold 60V; Fuse_1812_4532Metric
H1, H2: M2; MountingHole_2.2mm_M2
J1: harness cable; Molex_iGrid_501645-1820_2x09_P2.00mm_Vertical
J2: harness box; Molex_iGrid_501645-1820_2x09_P2.00mm_Vertical
J3: TYPE-C-31-M-12; USB_C_Receptacle_HRO_TYPE-C-31-M-12
JP1: TERM1 H; SolderJumper-2_P1.3mm_Open_RoundedPad1.0x1.5mm
JP2: TERM1 L; SolderJumper-2_P1.3mm_Open_RoundedPad1.0x1.5mm
JP3: TERM2 H; SolderJumper-2_P1.3mm_Open_RoundedPad1.0x1.5mm
JP4: TERM2 L; SolderJumper-2_P1.3mm_Open_RoundedPad1.0x1.5mm
JP5: TERM3 H; SolderJumper-2_P1.3mm_Open_RoundedPad1.0x1.5mm
JP6: TERM3 L; SolderJumper-2_P1.3mm_Open_RoundedPad1.0x1.5mm
K1, K2: G6K-2F-Y DC5; Relay_DPDT_Omron_G6K-2F-Y
L1: 6.8uH 2.75A; L_Sunlord_SWPA4030S
LOGO: leaf logo; leaf_logo
Q1: AO3400A; SOT-23
R1, R2, R3: 10k; R_0603_1608Metric
R4, R16: 1k; R_0603_1608Metric
R5, R6, R7, R8, R9, R10: 60.4; R_0603_1608Metric
R11, R12, R13, R17: 100k; R_0603_1608Metric
R14: 28k; R_0603_1608Metric
R15: 4.7k; R_0603_1608Metric
R18: 22k; R_0603_1608Metric
R19, R20: 5.1k; R_0603_1608Metric
SW1: DFU; SW_Push_1P1T_XKB_TS-1187A
TP1: SWDIO; TestPoint_Pad_D1.5mm
TP2: SWCLK; TestPoint_Pad_D1.5mm
TP3: NRST; TestPoint_Pad_D1.5mm
TP4: 3V3; TestPoint_Pad_D1.5mm
TP5, TP10: GND; TestPoint_Pad_D1.5mm
TP6: BOOT0; TestPoint_Pad_D1.5mm
TP7: VIN; TestPoint_Pad_D1.5mm
TP8: 5V_IGN; TestPoint_Pad_D1.5mm
TP9: 5V_SYS; TestPoint_Pad_D1.5mm
U1: STM32F413RGT6; LQFP-64_10x10mm_P0.5mm
U2, U3, U4: TJA1042T/3; SOIC-8_3.9x4.9mm_P1.27mm
U5: SN74LVC1G08DBVR; SOT-23-5
U6: TPS3828-33DBVR; SOT-23-5
U7: LMR16006YDDCR; SOT-23-6
U8: MCP1700T-3302E/TT; SOT-23-3
U9: USBLC6-2SC6; SOT-23-6
Y1: 8MHz 20pF; Crystal_SMD_5032-2Pin_5.0x3.2mm

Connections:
+3V3: C2.1, C3.1, C4.1, C5.1, C6.1, C7.1, C8.1, C9.1, C14.1, C17.1, C20.1, C22.1, C23.1, C33.1, D12.1, R1.1, R16.1, SW1.1, TP4.1, U1.1, U1.13, U1.19, U1.32, U1.48, U1.64, U2.5, U3.5, U4.5, U5.5, U6.3, U6.5, U8.2
+5V_IGN: C28.1, C29.1, C30.1, D5.1, D9.2, K1.A1, K2.A1, L1.2, R14.1, TP8.1
+5V_SYS: C13.1, C16.1, C19.1, C31.1, C32.1, D9.1, D10.1, TP9.1, U2.3, U3.3, U4.3, U8.3
BOOT0: R2.1, SW1.2, TP6.1, U1.60
BOOT1: R3.1, U1.28
BUCK_CB: C27.1, U7.1
BUCK_FB: R14.2, R15.1, U7.3
BUCK_SHDN: R13.2, U7.4
BUCK_SW: C27.2, D8.1, L1.1, U7.6
BUS0_LOOP_3: J1.3, J2.3
BUS0_LOOP_5: J1.5, J2.5
BUS2_LOOP_13: J1.13, J2.13
BUS2_LOOP_15: J1.15, J2.15
CAN0_H: J1.4, J2.4
CAN0_L: J1.6, J2.6
CAN1_ADAS_H: D21.1, J1.9, K1.11, U2.7
CAN1_ADAS_L: D21.2, J1.11, K1.21, U2.6
CAN1_CAR_H: D22.1, J1.8, J2.8, K1.12, K2.11, U3.7
CAN1_CAR_L: D22.2, J1.7, J2.7, K1.22, K2.21, U3.6
CAN1_RX: U1.61, U2.4
CAN1_STB: U1.9, U2.8
CAN1_TX: U1.62, U2.1
CAN2_H: D23.1, J1.16, J2.16, JP5.1, U4.7
CAN2_L: D23.2, J1.18, J2.18, JP6.1, U4.6
CAN2_RX: U1.57, U3.4
CAN2_STB: U1.2, U3.8
CAN2_TX: U1.58, U3.1
CAN3_RX: U1.41, U4.4
CAN3_STB: U1.14, U4.8
CAN3_TX: U1.50, U4.1
GND: C1.2, C2.2, C3.2, C4.2, C5.2, C6.2, C7.2, C8.2, C9.2, C10.2, C11.2, C12.2, C13.2, C14.2, C15.2, C16.2, C17.2, C18.2, C19.2, C20.2, C21.2, C22.2, C23.2, C24.2, C25.2, C26.2, C28.2, C29.2, C30.2, C31.2, C32.2, C33.2, C34.2, D1.1, D6.2, D8.2, D11.1, D21.3, D22.3, D23.3, J1.1, J1.17, J2.1, J2.17, J3.A1, J3.A12, J3.B1, J3.B12, J3.SH, Q1.2, R2.2, R3.2, R11.2, R12.2, R15.2, R18.2, R19.2, R20.2, TP5.1, TP10.1, U1.12, U1.18, U1.31, U1.47, U1.63, U2.2, U3.2, U4.2, U5.3, U6.2, U7.2, U8.1, U9.2
HSE_IN: C10.1, U1.5, Y1.1
HSE_OUT: C11.1, U1.6, Y1.2
IGN: F1.1, J1.2, J1.14, J2.2, J2.14
IGN_FUSED: D6.1, D7.2, F1.2
IGN_SENSE: C34.1, D12.2, R17.2, R18.1, U1.15
K1_NO_A: JP1.1, K1.14
K1_NO_B: JP2.1, K1.24
K2_NO_A: JP3.1, K2.14
K2_NO_B: JP4.1, K2.24
LED_STATUS: R4.1, U1.38
LED_STATUS_A: D1.2, R4.2
NRST: C12.1, R1.2, TP3.1, U1.7, U5.2, U6.1
PWR_LED_A: D11.2, R16.2
RELAY_COIL_LO: D5.2, K1.A2, K2.A2, Q1.3
RELAY_EN: R12.1, U1.33, U5.1
RELAY_GATE: Q1.1, R11.1, U5.4
SWCLK: TP2.1, U1.49
SWDIO: TP1.1, U1.46
TERM1_H: JP1.2, R5.1
TERM1_L: JP2.2, R6.2
TERM1_MID: C15.1, R5.2, R6.1
TERM2_H: JP3.2, R7.1
TERM2_L: JP4.2, R8.2
TERM2_MID: C18.1, R7.2, R8.1
TERM3_H: JP5.2, R9.1
TERM3_L: JP6.2, R10.2
TERM3_MID: C21.1, R9.2, R10.1
USB_CC1: J3.A5, R19.1
USB_CC2: J3.B5, R20.1
USB_DM: J3.A7, J3.B7, U1.44, U9.3, U9.4
USB_DP: J3.A6, J3.B6, U1.45, U9.1, U9.6
VBUS: D10.2, J3.A4, J3.A9, J3.B4, J3.B9, U9.5
VCAP_1: C1.1, U1.30
VIN12_10: J1.10, J2.10
VIN12_12: J1.12, J2.12
VIN_PROT: C24.1, C25.1, C26.1, D7.1, R13.1, R17.1, TP7.1, U7.5
WDT_KICK: U1.37, U6.4

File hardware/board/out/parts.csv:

Designator,Qty,Value,Manufacturer,MPN,LCSC,JLC,Stock 2026-11-27,Footprint
"C1,C8,C31,C33",4,4.7uF 16V,Samsung,CL10A475KO8NNNC,C19666,basic,2823038,Capacitor_SMD:C_0603_1608Metric
"C2,C3,C4,C5,C6,C7,C13,C14,C16,C17,C19,C20,C22,C23,C30,C34",16,100nF 16V,Samsung,CL05B104KO5NNNC,C1525,basic,28139937,Capacitor_SMD:C_0402_1005Metric
"C9,C32",2,1uF 25V,Samsung,CL05A105KA5NQNC,C52923,basic,11020353,Capacitor_SMD:C_0402_1005Metric
"C10,C11",2,30pF C0G,FH,0402CG300J500NT,C1570,preferred,176619,Capacitor_SMD:C_0402_1005Metric
C12,1,10nF 50V,Samsung,CL05B103KB5NNNC,C15195,basic,3704802,Capacitor_SMD:C_0402_1005Metric
"C15,C18,C21",3,4.7nF 50V,FH,0603B472K500NT,C53987,basic,1193387,Capacitor_SMD:C_0603_1608Metric
"C24,C25",2,2.2uF 50V X7R,YAGEO,CC0805KKX7R9BB225,C125847,extended,89345,Capacitor_SMD:C_0805_2012Metric
"C26,C27",2,100nF 50V,YAGEO,CC0603KRX7R9BB104,C14663,basic,44117980,Capacitor_SMD:C_0603_1608Metric
"C28,C29",2,22uF 25V,Samsung,CL21A226MAQNNNE,C45783,basic,4353392,Capacitor_SMD:C_0805_2012Metric
"D1,D11",2,red,KENTO,KT-0603R,C2286,basic,8430004,LED_SMD:LED_0603_1608Metric
"D5,D12",2,1N4148W,Semtech,1N4148W,C81598,basic,4126998,Diode_SMD:D_SOD-123
D6,1,SMBJ33A,Littelfuse,SMBJ33A,C224019,extended,23761,Diode_SMD:D_SMB
"D7,D8",2,SS210,MDD,SS210,C14996,basic,842768,Diode_SMD:D_SMA
"D9,D10",2,B5819W,CJ,B5819W SL,C8598,basic,1044236,Diode_SMD:D_SOD-123
"D21,D22,D23",3,PESD2CAN,Nexperia,"PESD2CAN,215",C75176,extended,47430,Package_TO_SOT_SMD:SOT-23
F1,1,500mA hold 60V,TECHFUSE,mSMD050-60V,C70113,extended,269194,Fuse:Fuse_1812_4532Metric
"J1,J2",2,501645-1820,Molex,5016451820,C504976,extended,5760,leaf_gw:Molex_iGrid_501645-1820_2x09_P2.00mm_Vertical
J3,1,TYPE-C-31-M-12,HRO,TYPE-C-31-M-12,C165948,extended,393127,Connector_USB:USB_C_Receptacle_HRO_TYPE-C-31-M-12
"K1,K2",2,G6K-2F-Y DC5,Omron,G6K-2F-Y-5V,C2982926,extended,35487,Relay_SMD:Relay_DPDT_Omron_G6K-2F-Y
L1,1,6.8uH 2.75A,Sunlord,SWPA4030S6R8MT,C62684,extended,20484,Inductor_SMD:L_Sunlord_SWPA4030S
Q1,1,AO3400A,AOS,AO3400A,C20917,basic,1303752,Package_TO_SOT_SMD:SOT-23
"R1,R2,R3",3,10k,UNI-ROYAL,0603WAF1002T5E,C25804,basic,38840366,Resistor_SMD:R_0603_1608Metric
"R4,R16",2,1k,UNI-ROYAL,0603WAF1001T5E,C21190,basic,36313912,Resistor_SMD:R_0603_1608Metric
"R5,R6,R7,R8,R9,R10",6,60.4,UNI-ROYAL,0603WAF604JT5E,C23090,extended,17967,Resistor_SMD:R_0603_1608Metric
"R11,R12,R13,R17",4,100k,UNI-ROYAL,0603WAF1003T5E,C25803,basic,13791470,Resistor_SMD:R_0603_1608Metric
R14,1,28k,UNI-ROYAL,0603WAF2802T5E,C22989,extended,102251,Resistor_SMD:R_0603_1608Metric
R15,1,4.7k,UNI-ROYAL,0603WAF4701T5E,C23162,basic,18075861,Resistor_SMD:R_0603_1608Metric
R18,1,22k,UNI-ROYAL,0603WAF2202T5E,C31850,basic,2006051,Resistor_SMD:R_0603_1608Metric
"R19,R20",2,5.1k,UNI-ROYAL,0603WAF5101T5E,C23186,basic,17262608,Resistor_SMD:R_0603_1608Metric
SW1,1,TS-1187A,XKB,TS-1187A-B-A-B,C318884,basic,634624,Button_Switch_SMD:SW_Push_1P1T_XKB_TS-1187A
U1,1,STM32F413RGT6,ST,STM32F413RGT6,C468260,extended,11,Package_QFP:LQFP-64_10x10mm_P0.5mm
"U2,U3,U4",3,TJA1042T/3,NXP,TJA1042T/3/1J,C132227,extended,37294,Package_SO:SOIC-8_3.9x4.9mm_P1.27mm
U5,1,SN74LVC1G08DBVR,TI,SN74LVC1G08DBVR,C7666,extended,94527,Package_TO_SOT_SMD:SOT-23-5
U6,1,TPS3828-33DBVR,TI,TPS3828-33DBVR,C20032,extended,41300,Package_TO_SOT_SMD:SOT-23-5
U7,1,LMR16006YDDCR,TI,LMR16006YDDCR,C290195,extended,16130,Package_TO_SOT_SMD:SOT-23-6
U8,1,MCP1700T-3302E/TT,Microchip,MCP1700T-3302E/TT,C39051,extended,23887,Package_TO_SOT_SMD:SOT-23-3
U9,1,USBLC6-2SC6,ST,USBLC6-2SC6,C7519,extended,27004,Package_TO_SOT_SMD:SOT-23-6
Y1,1,8MHz 20pF,YXC,X50328MSB2GI,C115962,basic,506868,Crystal:Crystal_SMD_5032-2Pin_5.0x3.2mm

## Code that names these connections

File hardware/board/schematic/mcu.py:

"""STM32F413RGT6 (SPEC.md "MCU"), pins as the Ocelot gateway
(RetroPilot firmware/boards/gateway.h): CAN1 PB8/PB9, CAN2 PB5/PB6,
CAN3 PA8/PA15, standby PC1/PC13/PA0, IGN PA1, relay PB12. Our picks:
watchdog kick PC6, status LED PC7.
"""

from skidl import Net

from nets import nc
from parts import nobom, part

SIGNALS = {
    "PB8": "CAN1_RX", "PB9": "CAN1_TX",
    "PB5": "CAN2_RX", "PB6": "CAN2_TX",
    "PA8": "CAN3_RX", "PA15": "CAN3_TX",
    "PC1": "CAN1_STB", "PC13": "CAN2_STB", "PA0": "CAN3_STB",
    "PA1": "IGN_SENSE", "PB12": "RELAY_EN",
    "PC6": "WDT_KICK", "PC7": "LED_STATUS",
    "PA11": "USB_DM", "PA12": "USB_DP",
    "PA13": "SWDIO", "PA14": "SWCLK",
    "PH0": "HSE_IN", "PH1": "HSE_OUT",
    "PB2": "BOOT1",
}


def cap(key, net, gnd):
    c = part(key)
    c[1] += net
    c[2] += gnd


def build(n):
    u = part("MCU", ref="U1")
    for pin, net in SIGNALS.items():
        u[pin] += getattr(n, net)
    for pin in u.pins:
        if pin.name in ("VDD", "VBAT", "VDDA"):
            pin += n.P3V3
        elif pin.name in ("VSS", "VSSA"):
            pin += n.GND
    vcap = Net("VCAP_1")
    u["VCAP_1"] += vcap
    cap("C_4u7", vcap, n.GND)  # VCAP_1: 4.7 uF low-ESR (STM32F413 datasheet, VCAP_1 note)
    u["NRST"] += n.NRST
    u["BOOT0"] += n.BOOT0

    # decoupling: 100 nF per VDD pin (4) + VBAT + VDDA, bulk 4.7 uF, VDDA 1 uF
    for _ in range(6):
        cap("C_100n", n.P3V3, n.GND)
    cap("C_4u7", n.P3V3, n.GND)
    cap("C_1u", n.P3V3, n.GND)

    # HSE 8 MHz, CL 20 pF: 2 x (20 - ~5 pF stray) = 30 pF
    y = part("Y_8M", ref="Y1")
    y[1] += n.HSE_IN
    y[2] += n.HSE_OUT
    cap("C_30p", n.HSE_IN, n.GND)
    cap("C_30p", n.HSE_OUT, n.GND)

    # reset: 10k pull-up (the watchdog output is open drain), 10 nF: small enough that
    # the MCU's own 20 us reset pulse pulls NRST below VIL (DS11581 fig. 37 note 2),
    # so its internal resets also reach the relay's AND gate
    r = part("R_10k")
    r[1] += n.P3V3
    r[2] += n.NRST
    cap("C_10n", n.NRST, n.GND)

    # boot: BOOT0 pulled down, button to 3V3 for ROM DFU; BOOT1 (PB2) low
    for net in (n.BOOT0, n.BOOT1):
        r = part("R_10k")
        r[1] += net
        r[2] += n.GND
    sw = part("SW_push", ref="SW1", value="DFU")
    sw[1] += n.P3V3
    sw[2] += n.BOOT0

    # status LED
    r = part("R_1k")
    r[1] += n.LED_STATUS
    r[2] += n.LED_STATUS_A
    led = part("LED_red", value="STATUS")
    led["A"] += n.LED_STATUS_A
    led["K"] += n.GND

    # SWD + boot test pads
    for name, net in (("SWDIO", n.SWDIO), ("SWCLK", n.SWCLK), ("NRST", n.NRST),
                      ("3V3", n.P3V3), ("GND", n.GND), ("BOOT0", n.BOOT0)):
        tp = nobom("TP", name)
        tp[1] += net

    used = set(SIGNALS)
    for pin in u.pins:
        if pin.name.startswith("P") and pin.name not in used:
            nc(pin, "spare GPIO")

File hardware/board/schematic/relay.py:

"""Fail-open relay and its gating (SPEC.md "Fail-open relay").

K1 de-energized: each pole's NC contact joins the ADAS-side and car-side
Chassis CAN line (pole A = H, pole B = L), so the car runs stock. The coil is
energized only while RELAY_EN (PB12) is high AND the watchdog's RESET output
(on NRST) is high. Omron G6K-2F-Y terminals (en-g6k.pdf p.6): 1 coil+, 8 coil-,
3/6 COM, 2/7 NC, 4/5 NO; KiCad's symbol/footprint call them A1, A2, 11/21,
12/22, 14/24.

The NO contacts switch the CAN1 split terminations (can.py): K1's put the
ADAS-side termination on CAN1_ADAS, and K2, a second G6K-2F-Y with its coil in
parallel with K1's, puts the car-side one on CAN1_CAR. De-energized, both
terminations hang off open contacts and the joined bus sees neither.
"""

from nets import nc
from parts import part


def build(n):
    k = part("RELAY", ref="K1")
    k["11"] += n.CAN1_ADAS_H  # pole A COM (datasheet pin 3)
    k["12"] += n.CAN1_CAR_H   # pole A NC  (pin 2)
    k["21"] += n.CAN1_ADAS_L  # pole B COM (pin 6)
    k["22"] += n.CAN1_CAR_L   # pole B NC  (pin 7)
    k["14"] += n.K1_NO_A      # pole A NO (pin 4): ADAS-side termination, H leg
    k["24"] += n.K1_NO_B      # pole B NO (pin 5): ADAS-side termination, L leg
    k["A1"] += n.P5V_IGN       # coil+ only from IGN, so USB power alone stays in passthrough
    k["A2"] += n.RELAY_COIL_LO

    # K2: car-side termination switch, coil in parallel with K1 (one driver,
    # one flyback diode: 2 x 21.1 mA, en-g6k.pdf p.3)
    k2 = part("RELAY", ref="K2")
    k2["11"] += n.CAN1_CAR_H  # pole A COM
    k2["14"] += n.K2_NO_A     # pole A NO: car-side termination, H leg
    k2["21"] += n.CAN1_CAR_L  # pole B COM
    k2["24"] += n.K2_NO_B     # pole B NO: car-side termination, L leg
    nc(k2["12"], "K2 NC, pole A: de-energized = no car-side termination")
    nc(k2["22"], "K2 NC, pole B: de-energized = no car-side termination")
    k2["A1"] += n.P5V_IGN
    k2["A2"] += n.RELAY_COIL_LO

    flyback = part("D_1N4148W")
    flyback["K"] += n.P5V_IGN
    flyback["A"] += n.RELAY_COIL_LO

    q = part("NMOS", ref="Q1")
    q["D"] += n.RELAY_COIL_LO
    q["S"] += n.GND
    q["G"] += n.RELAY_GATE
    r = part("R_100k")  # gate pull-down: off while the AND gate is unpowered
    r[1] += n.RELAY_GATE
    r[2] += n.GND

    gate = part("AND", ref="U5")
    gate[1] += n.RELAY_EN   # A: MCU relay enable
    gate[2] += n.NRST       # B: watchdog RESET (open drain, shared with MCU NRST)
    gate[4] += n.RELAY_GATE
    gate["VCC"] += n.P3V3
    gate["GND"] += n.GND
    c = part("C_100n")
    c[1] += n.P3V3
    c[2] += n.GND
    r = part("R_100k")  # RELAY_EN pull-down: PB12 floats in reset / unprogrammed
    r[1] += n.RELAY_EN
    r[2] += n.GND

    # Watchdog: RESET goes low for ~200 ms if WDI has no edge for 0.9-2.5 s
    # (SLVS165O 6.8). Open drain on NRST, so the MCU's own resets also drop
    # the relay. WDI has no pull on purpose: floating (MCU in reset, ROM DFU,
    # SWD reset-halt) disables the timer (SLVS165O 7.3.4), so the board can be
    # flashed; PB12's pull-down keeps the relay off in those states.
    wdt = part("WDT", ref="U6")
    wdt[1] += n.NRST
    wdt["GND"] += n.GND
    wdt[3] += n.P3V3        # MR unused: tie to VDD (pin table)
    wdt["WDI"] += n.WDT_KICK
    wdt[5] += n.P3V3
    c = part("C_100n")
    c[1] += n.P3V3
    c[2] += n.GND

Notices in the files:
hardware/board/layout/leaf_gw.kicad_pcb:
© 2026 Stephen Bouche · MIT
